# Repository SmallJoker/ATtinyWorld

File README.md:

## ATtiny World

A collection of libraries to make use of an ATtiny2313 MCU.

* [Datasheet](https://ww1.microchip.com/downloads/en/DeviceDoc/Atmel-2543-AVR-ATtiny2313_Datasheet.pdf)

### Setup

This repository assumes that a Debian-based distro is used. Package names may vary.

#### 1. Used programmers

* USBtinyISP
    * [Introduction](https://learn.adafruit.com/usbtinyisp/use-it)
    * [Schematic](https://cdn-learn.adafruit.com/assets/assets/000/010/326/original/usbtinyisp2sch.png)
    * [Tutorial including firmware](https://cdn-learn.adafruit.com/downloads/pdf/usbtinyisp.pdf)

#### 2. Required packages

* `gcc-avr`
* `avr-libc`
* `avrdude`

#### 3. Initial MCU fuse setup

Note: the fuse bits are inverted! 0 = selected

* Documentation chapter "Fuse Bits"
* Configuration tool: https://www.engbedded.com/fusecalc/

Example configuration:

    # 0xE4 : 8 MHz clock, slow start
    avrdude -c usbtiny -p t2313 -i 400 -U lfuse:w:0xE4:m
    # 0xDF : SPI flash enable
    avrdude -c usbtiny -p t2313 -i 400 -U hfuse:w:0xDF:m

#### Serial terminal apps (RS232)

* `cutecom`
* [hterm](http://der-hammer.info/pages/terminal.html)

### Licenses

 * Code: MIT
 * Other: CC-BY-SA 4.0

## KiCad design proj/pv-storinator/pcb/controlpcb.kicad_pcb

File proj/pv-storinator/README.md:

# pv-storinator

This project is about powering a Single Board Computer (SBC) from a photovoltaic (PV) panel.
The hardware documented in this repository was not tested against any safety standards.

**Use-cases:**

* Simple battery charger
    * Use the option `#define HAVE_OUTPUT (0)`
* Weather logging station
* Minimalist game or web server
* ???

**Used applications and blueprints:**

* Schematics: [KiCad 9.0.1](https://www.kicad.org/)
* Diagrams: [draw.io](https://app.diagrams.net/)
* From the *examples* directory of this repository:
    * Hardware: Current Sense, Ideal Diode
    * Software: PWM ADC, USART RS232 (WIP)
* DC/DC converter: recycled boards

## Project progress

* &#10004; MCU state machine
* &#10004; MCU pin mapping
* &#10004; Schematic
* &#10004; Layout
* &#10004; Firmware implementation + Dry run testing
* Interface script
* Real-world testing

## Requirements

* PV/Input voltage: 0 V ... 25 V
* PV/Input current: 0 A ... 1.5 A
* Battery undervoltage protection
* Battery overvoltage protection
* Constant Current (CC) charging
* Maximum Power Point Tracking (MPPT) for the PV panel

## Development notes

To visualize MCU activity, the TXD signal can be used to flash an LED.
The duty-cycle is < 1 %, thus connecting an LED + R directly to TXD would not produce a well visible blinking light.

### Bugs in 2025-07-26

* Schematic: U2.2/6 should connect to `PWM_0A_DC`

## Monitor script

**Dependencies**

* `serial` (apt `python3-serial`)

**Usage:**

* `python3 monitor.py /dev/ttyS`

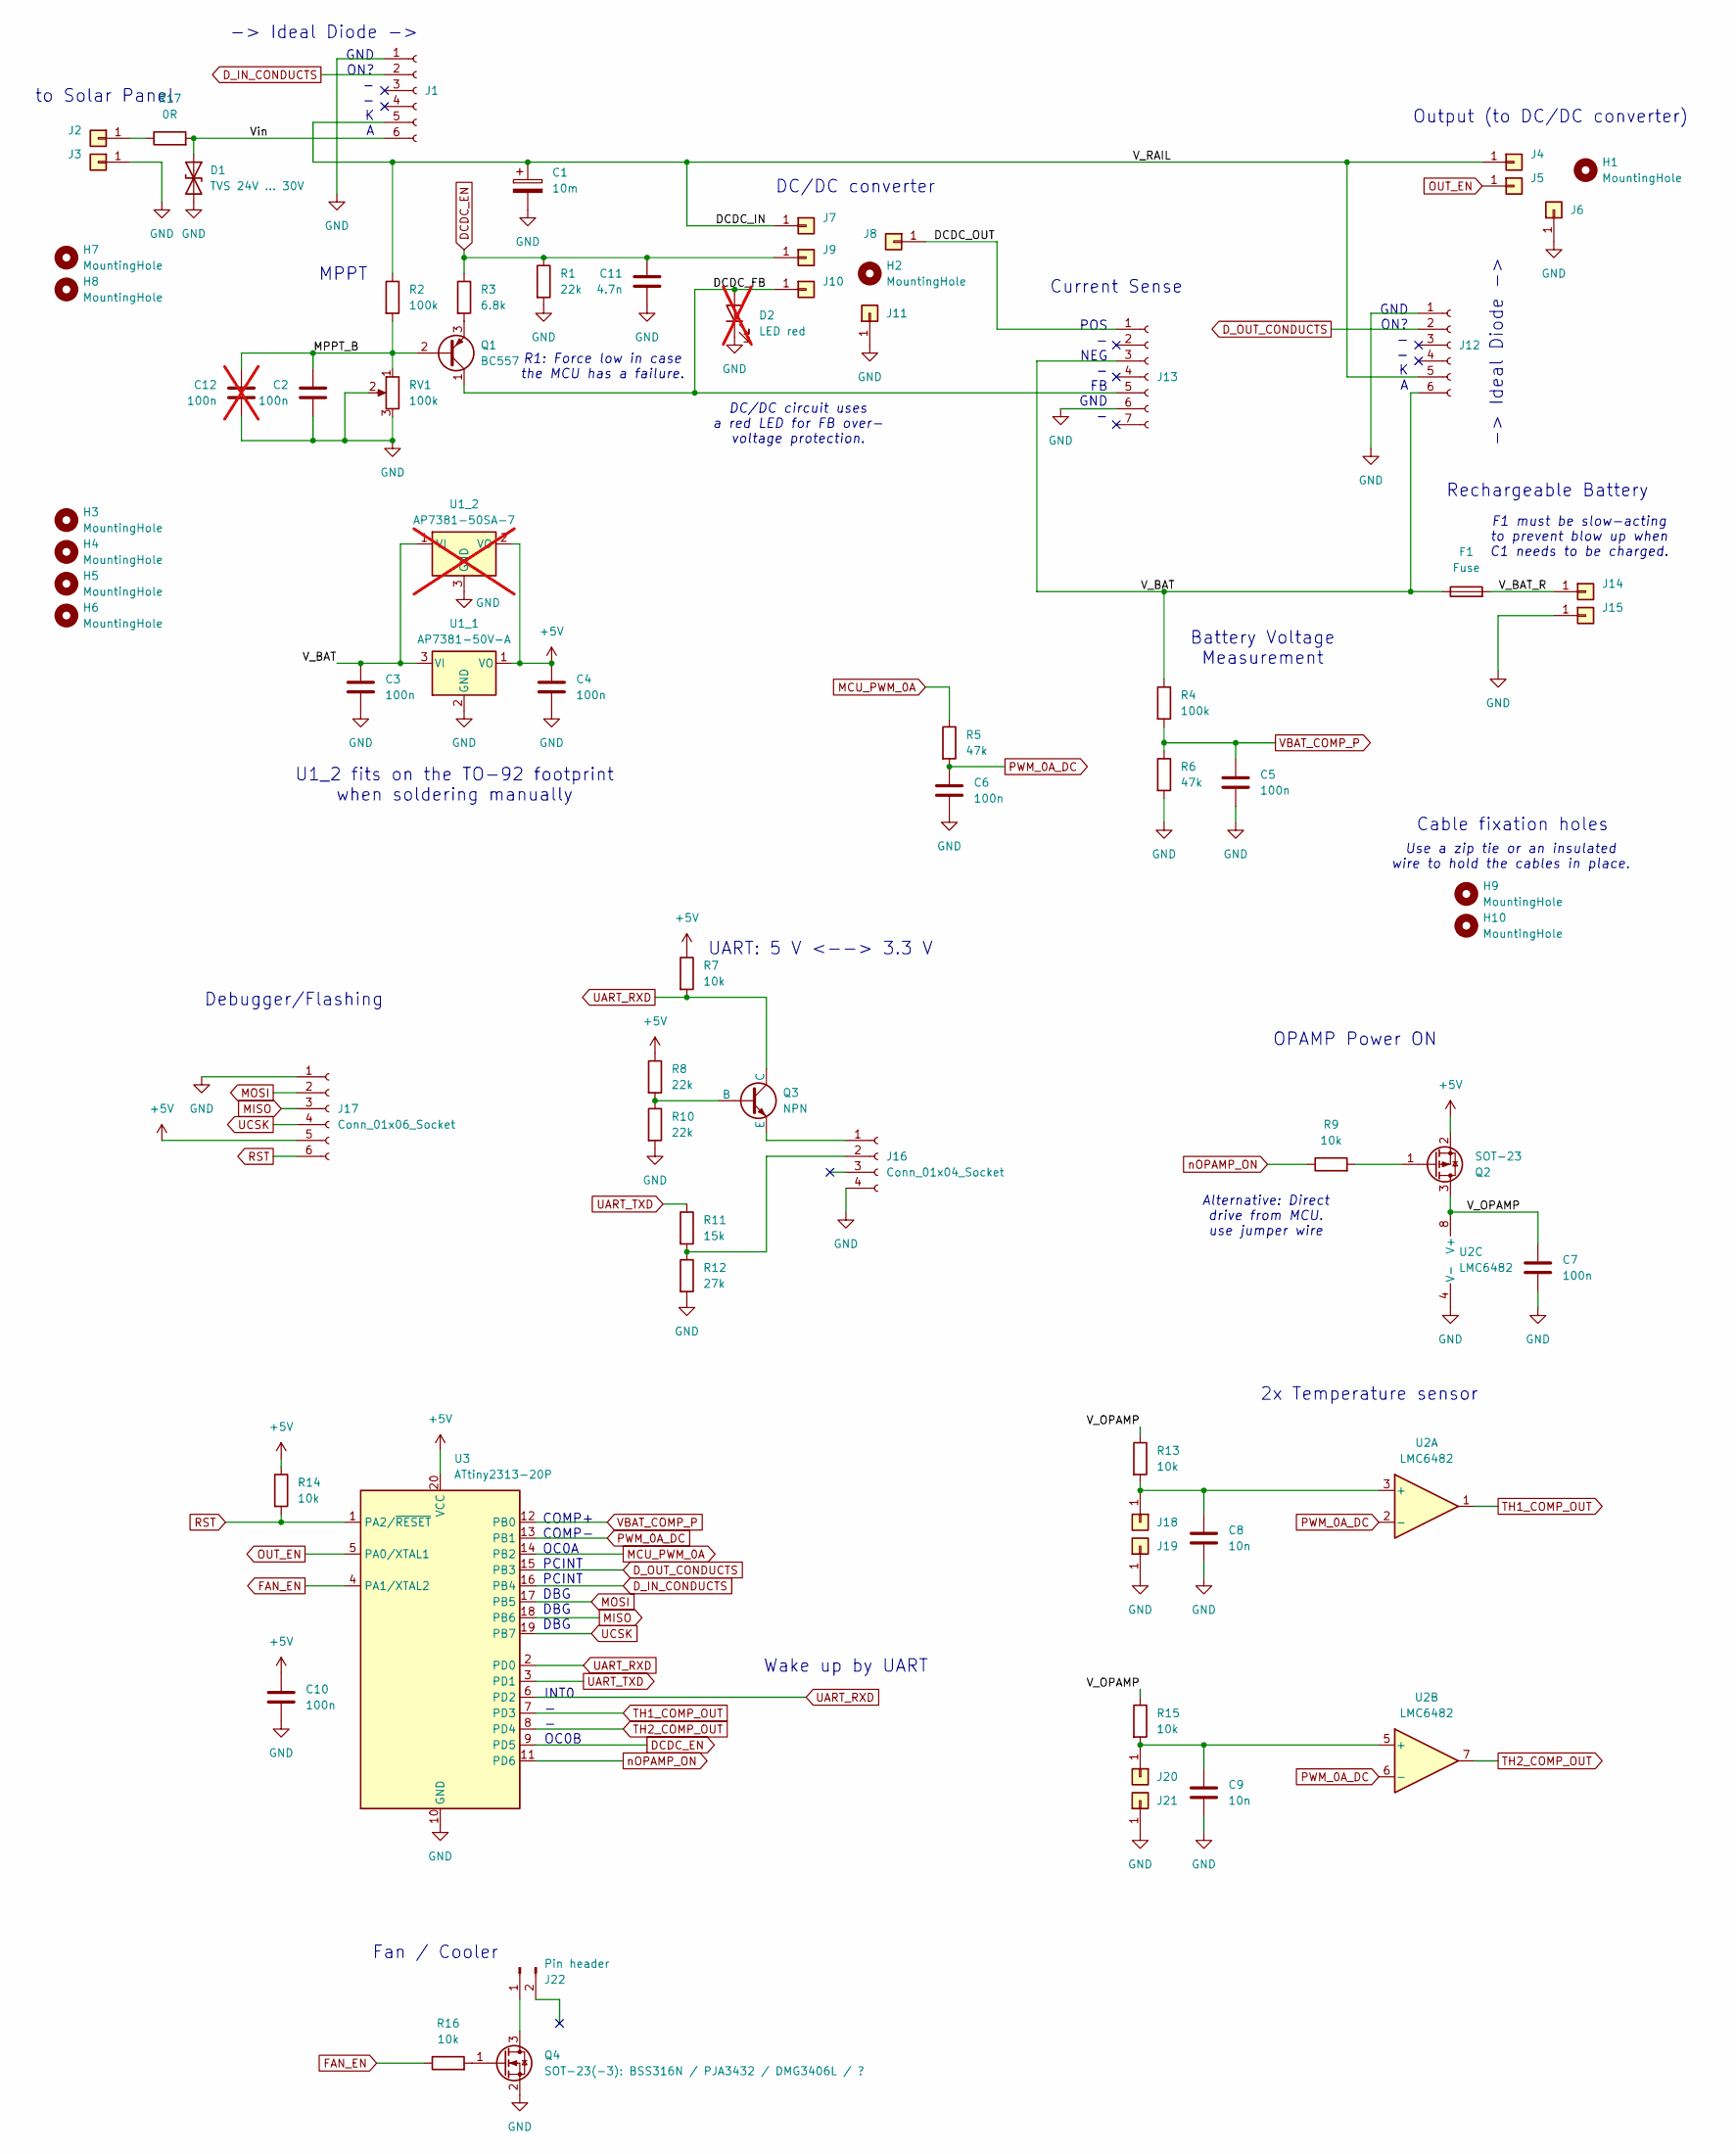
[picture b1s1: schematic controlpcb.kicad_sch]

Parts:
C1: 10m; CP_Radial_D30.0mm_P10.00mm_SnapIn
C2, C3, C4, C5, C6: 100n; C_0805_2012Metric_Pad1.18x1.45mm_HandSolder
C7: 100n; C_0805_2012Metric
C8, C9: 10n; C_0805_2012Metric
C10: 100n; C_Rect_L7.0mm_W3.5mm_P5.00mm
C11: 4.7n; C_0805_2012Metric_Pad1.18x1.45mm_HandSolder
C12: 100n; C_0805_2012Metric_Pad1.18x1.45mm_HandSolder; not fitted
D1: TVS 24V ... 30V; D_SMA-SMB_Universal_Handsoldering
D2: LED red; LED_0603_1608Metric; not fitted
F1: Fuse; Fuseholder_Clip-5x20mm_Littelfuse_445-030_Inline_P20.50x5.2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
H1, H2, H3, H4, H5, H6: MountingHole; MountingHole_3.2mm_M3_ISO7380
H7, H8, H9, H10: MountingHole; MountingHole_2.5mm
J1, J12: Conn_01x06_Socket; SIP-6_Upright_Board
J2, J3, J4, J6, J7, J8, J11, J14, J15: Conn_01x01; SolderWire-0.75sqmm_1x01_D1.25mm_OD2.3mm
J5, J9, J10: Conn_01x01; SolderWire-0.5sqmm_1x01_D0.9mm_OD2.1mm
J13: Conn_01x07_Socket; SIP-7_Upright_Board
J16: Conn_01x04_Socket; PinSocket_1x04_P2.54mm_Vertical
J17: Conn_01x06_Socket; PinSocket_1x06_P2.54mm_Vertical
J18, J19, J20, J21: Conn_01x01; PinHeader_1x01_P2.54mm_Vertical
J22: Pin header; PinHeader_1x02_P2.54mm_Vertical
Q1: BC557; TO-92_W
Q2: SOT-23
Q3: NPN; TO-92_W
Q4: SOT-23(-3): BSS316N / PJA3432 / DMG3406L / ?; SOT-23-3
R1, R8, R10: 22k; R_0805_2012Metric
R2: 100k; R_Axial_DIN0207_L6.3mm_D2.5mm_P5.08mm_Vertical
R3: 6.8k; R_Axial_DIN0207_L6.3mm_D2.5mm_P2.54mm_Vertical
R4: 100k; R_Axial_DIN0207_L6.3mm_D2.5mm_P10.16mm_Horizontal
R5, R6: 47k; R_Axial_DIN0207_L6.3mm_D2.5mm_P2.54mm_Vertical
R7, R9, R16: 10k; R_0805_2012Metric_Pad1.20x1.40mm_HandSolder
R11: 15k; R_0805_2012Metric
R12: 27k; R_0805_2012Metric
R13: 10k; R_Axial_DIN0207_L6.3mm_D2.5mm_P15.24mm_Horizontal
R14: 10k; R_Axial_DIN0207_L6.3mm_D2.5mm_P5.08mm_Vertical
R15: 10k; R_Axial_DIN0207_L6.3mm_D2.5mm_P2.54mm_Vertical
R17: 0R; R_0805_2012Metric_Pad1.20x1.40mm_HandSolder
RV1: 100k; Potentiometer_Vishay_T73XX_Horizontal
U1_1: AP7381-50V-A; TO-92_W
U1_2: AP7381-50SA-7; SOT-23; not fitted
U2: LMC6482; SOIC-8_5.3x6.2mm_P1.27mm
U3: ATtiny2313-20P; DIP-20_W7.62mm

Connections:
+5V: C4.1, C10.1, J17.5, Q2.2 (S), R7.1, R8.1, R14.1, U1_1.1 (VO), U1_2.2 (VO), U3.20 (VCC)
/DCDC_FB: D2.2 (A), J10.1, J13.5, Q1.1 (C)
/DCDC_IN: C1.1, J1.5, J4.1, J7.1, J12.5, R2.1
/DCDC_OUT: J8.1, J13.1
/MPPT_B: C2.1, C12.1, Q1.2 (B), R2.2, RV1.1
/V_BAT: C3.1, F1.1, J12.6, J13.3, R4.1, U1_1.3 (VI), U1_2.1 (VI)
/V_BAT_R: F1.2, J14.1
/V_OPAMP: C7.1, Q2.3 (D), R13.1, R15.1, U2.8 (V+)
/Vin: D1.1 (A1), J1.6, R17.2
DCDC_EN: C11.1, J9.1, R1.1, R3.1, U3.9 (PD5)
D_IN_CONDUCTS: J1.2, U3.16 (PB4)
D_OUT_CONDUCTS: J12.2, U3.15 (PB3)
FAN_EN: R16.1, U3.4 (PA1/XTAL2)
GND: C1.2, C2.2, C3.2, C4.2, C5.2, C6.2, C7.2, C8.2, C9.2, C10.2, C11.2, C12.2, D1.2 (A2), D2.1 (K), J1.1, J3.1, J6.1, J11.1, J12.1, J13.6, J15.1, J16.4, J17.1, J19.1, J21.1, Q4.2 (S), R1.2, R6.2, R10.2, R12.2, RV1.2, RV1.3, U1_1.2 (GND), U1_2.3 (GND), U2.4 (V-), U3.10 (GND)
MCU_PWM_0A: R5.1, U3.14 (PB2)
MISO: J17.3, U3.18 (PB6)
MOSI: J17.2, U3.17 (PB5)
unnamed: J2.1, R17.1
unnamed: J16.1, Q3.3 (E)
unnamed: J16.2, R11.2, R12.1
unnamed: C8.1, J18.1, R13.2, U2.3 (+)
unnamed: C9.1, J20.1, R15.2, U2.5 (+)
unnamed: J22.1, Q4.3 (D)
unnamed: Q1.3 (E), R3.2
unnamed: Q2.1 (G), R9.2
unnamed: Q3.2 (B), R8.2, R10.1
unnamed: Q4.1 (G), R16.2
OUT_EN: J5.1, U3.5 (PA0/XTAL1)
PWM_0A_DC: C6.1, R5.2, U2.2 (-), U2.6 (-), U3.13 (PB1)
RST: J17.6, R14.2, U3.1 (PA2/~RESET)
TH1_COMP_OUT: U2.1, U3.7 (PD3)
TH2_COMP_OUT: U2.7, U3.8 (PD4)
UART_RXD: Q3.1 (C), R7.2, U3.2 (PD0), U3.6 (PD2)
UART_TXD: R11.1, U3.3 (PD1)
UCSK: J17.4, U3.19 (PB7)
VBAT_COMP_P: C5.1, R4.2, R6.1, U3.12 (PB0)
nOPAMP_ON: R9.1, U3.11 (PD6)

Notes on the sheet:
Output (to DC/DC converter)
DC/DC converter
MPPT
INT0 - - OC0B
to Solar Panel
U1_2 fits on the TO-92 footprint when soldering manually
Fan / Cooler
OPAMP Power ON
Current Sense
Use a zip tie or an insulated wire to hold the cables in place.
F1 must be slow-acting to prevent blow up when C1 needs to be charged.
GND ON? - - K A
Rechargeable Battery
Debugger/Flashing
R1: Force low in case the MCU has a failure.
COMP+ COMP- OC0A PCINT PCINT DBG DBG DBG
-> Ideal Diode ->
POS - NEG - FB GND -
DC/DC circuit uses a red LED for FB over- voltage protection.
Battery Voltage Measurement
UART: 5 V <--> 3.3 V
2x Temperature sensor
Wake up by UART
Cable fixation holes
Alternative: Direct drive from MCU. use jumper wire

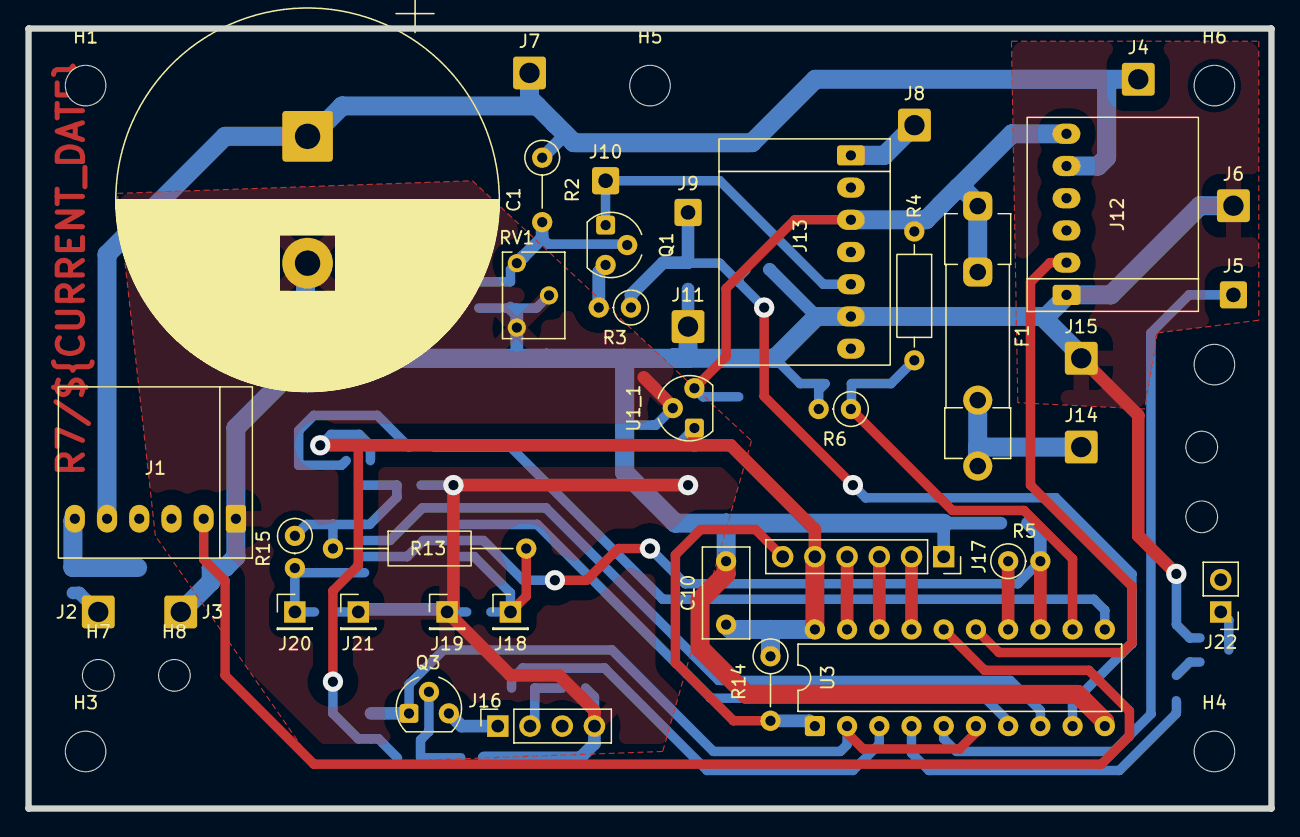
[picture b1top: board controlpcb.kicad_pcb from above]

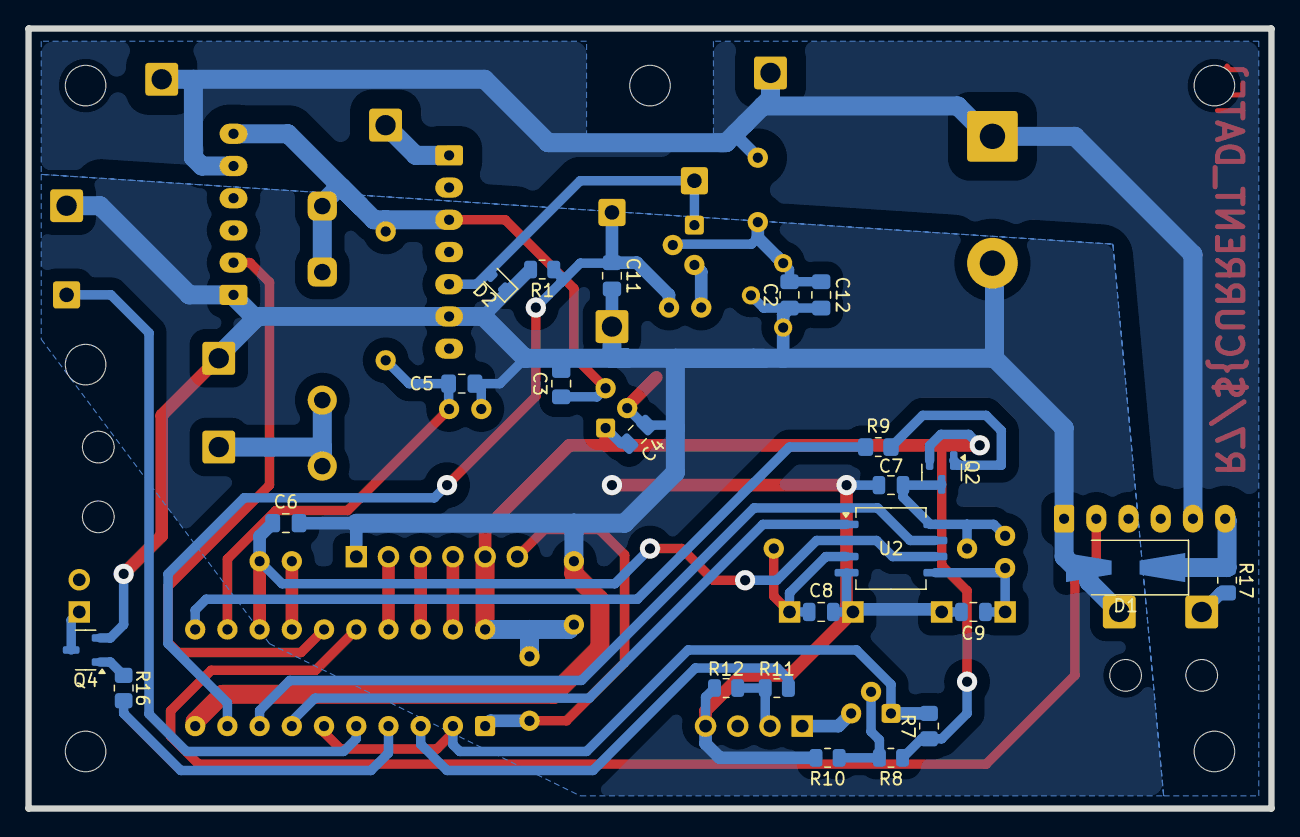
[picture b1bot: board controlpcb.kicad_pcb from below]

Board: 2 copper layers, 98.0 x 61.5 mm, 72 parts (24 on the bottom side), 37 nets.

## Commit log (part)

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2023-12-09 Upload USART RS232 (buffered)
2024-02-09 Add CMake project template
    To run all: make TARGET_NAME_flash
2024-02-11 Add PWM-based ADC with example
2024-03-02 Dual Slope ADC (almost)
2024-07-25 Provide simulation schematics
2025-04-05 Improve documentation and build flags
2025-05-29 Revise Ideal Diode circuit
    This time with a prototype and measurement results.
2025-06-29 Add current sense circuit
2025-07-03 Initial version of the pv-storinator
2025-07-04 pv-storinator: Add firmware skeleton
2025-07-14 pv-storinator: Watchdog/sleep functionality
2025-07-15 pv-storinator: Implement UART commands and state machine
    Program: 1132 bytes (55.3% Full)
    Data: 11 bytes (8.6% Full)
2025-07-19 pv-storinator: Improve mounting holes and R5 + R6 values
2025-07-19 pv-storinator: Upload FW documentation and several corrections
    Program: 1196 bytes (58.4% Full)
    Data: 11 bytes (8.6% Full)
2025-07-20 pv-storinator: Improve voltage measurement
    Previously, the aux. OPAMP did power itself (a little bit)
    through the protection diodes, using MCU_PWM_0A.
2025-07-26 pv-storinator: Minor schematic improvements
    - More efficient voltage regulator (lower quiescent current)
    - SMD alternatives (hand soldering)
    - Pull-Down on charge DC/DC for safety
2025-08-02 pv-storinator: Fix up stupid PIN/PORT confusion
    This also adds a simple script to retrieve the battery voltage.
2025-11-08 Make avr-target compatible with binutils-avr 2.43.50
2026-03-21 pv-storinator: Improve ADC stability
    Previously, the sampled values alternated between two values.
    This fixes it by only returning the higher value.
2026-04-03 pv-storinator: Add TH1 measurement and threshold
    + New option 'HAVE_OUTPUT' to only charge batteries
2026-05-11 Add Step-up converter circuit
2026-05-11 Fix links
2026-06-23 pv-storinator: Improve PCB
    - Fix incorrect MCU_PWM_0A connection
    - Add TVS (suppressor) diode for safety
    - Enlarge holes for easier cable mounting
    - Add custom footprint library (previously missing)
